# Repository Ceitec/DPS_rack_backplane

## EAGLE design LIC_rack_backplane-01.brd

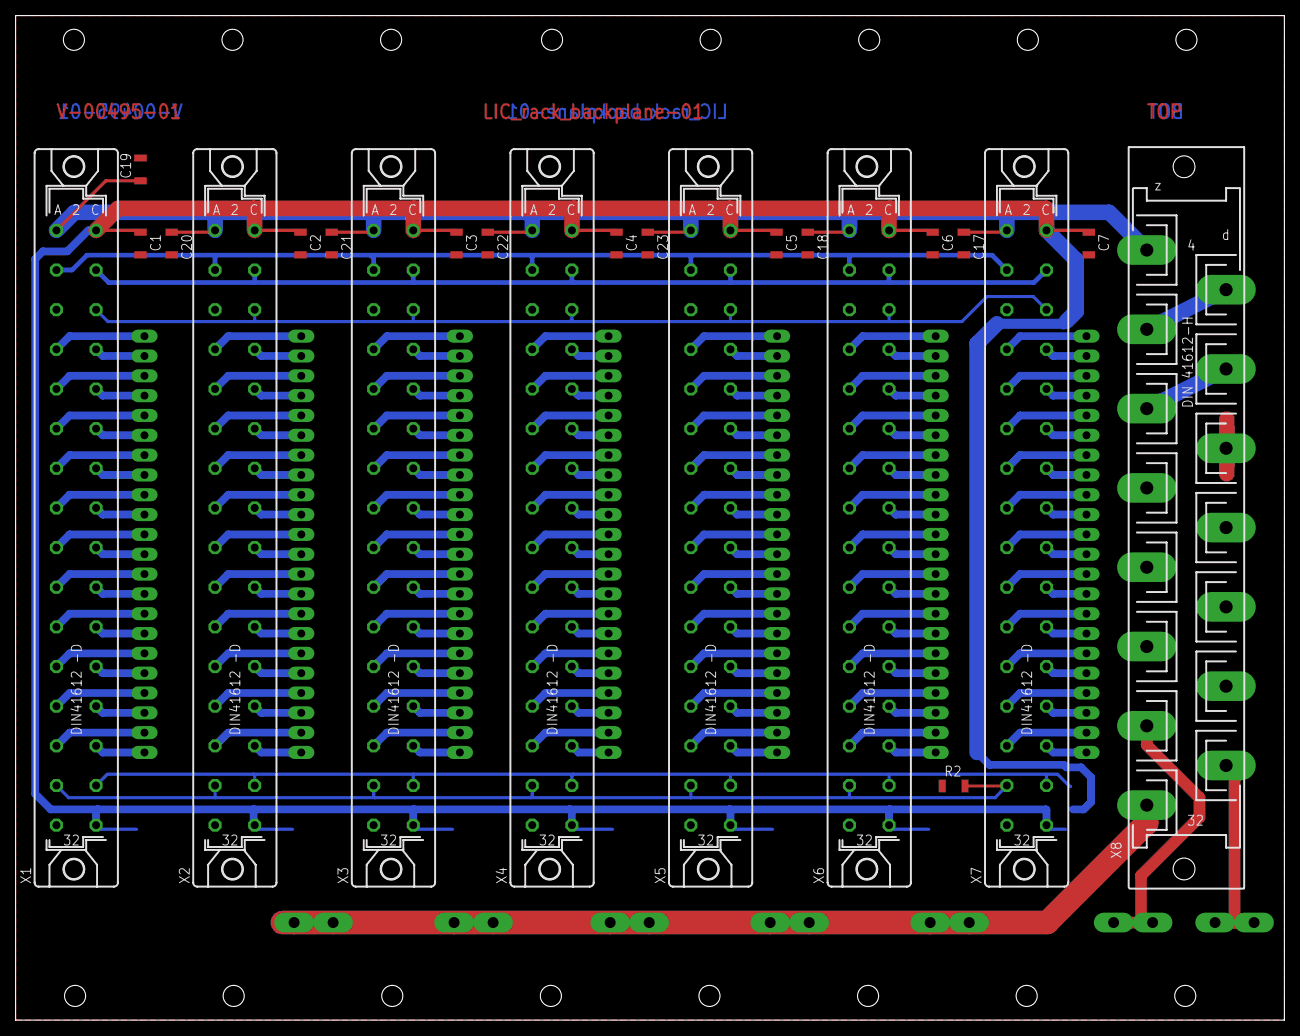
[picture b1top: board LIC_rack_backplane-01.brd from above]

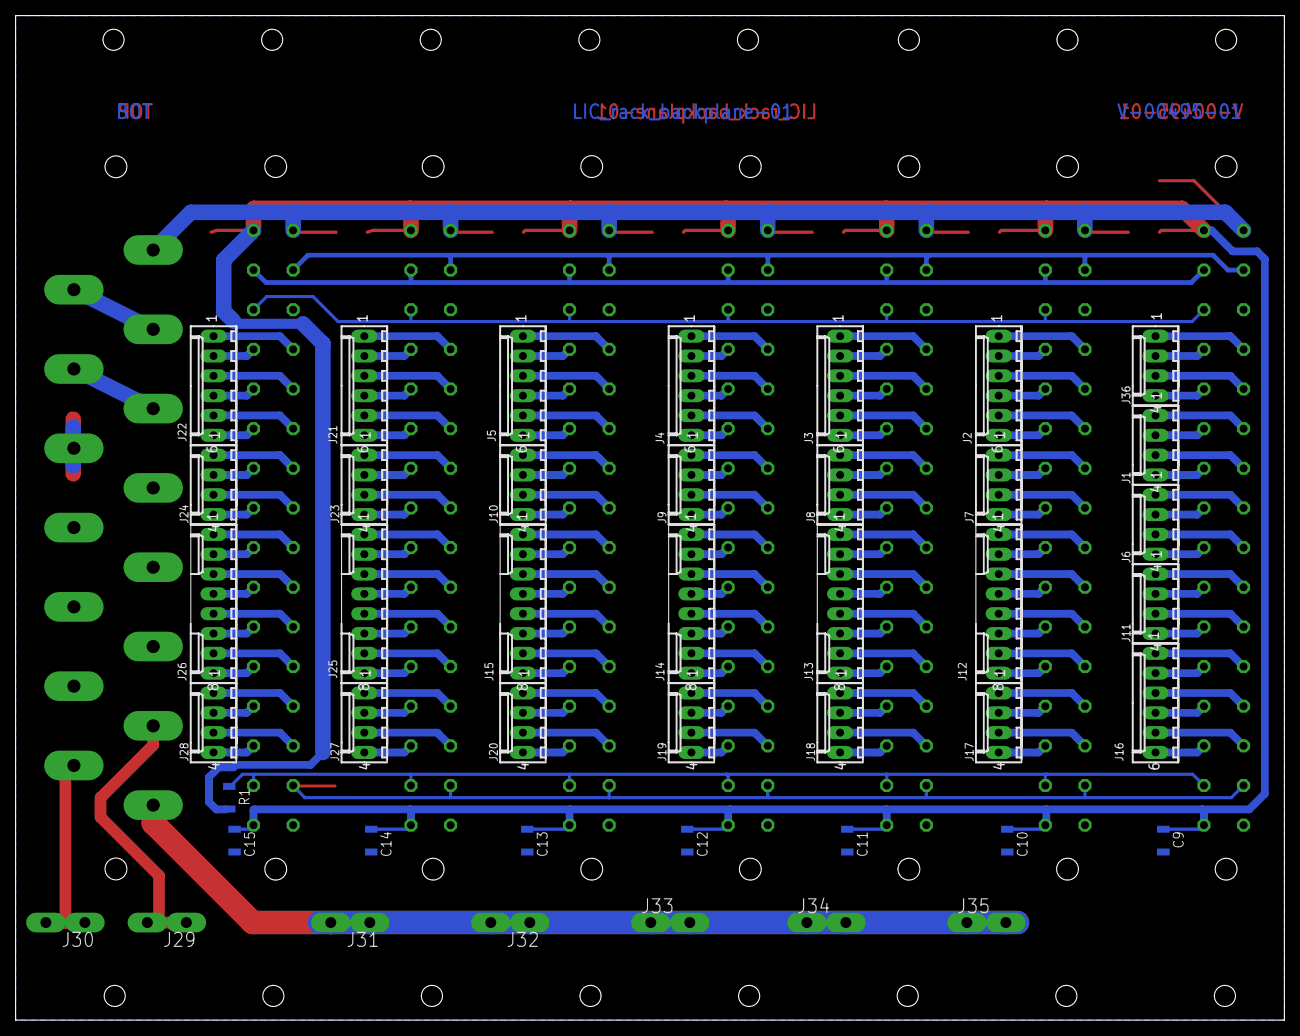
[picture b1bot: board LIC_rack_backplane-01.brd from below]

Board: 2 copper layers, 162.6 x 128.7 mm, 67 parts (44 on the bottom side), 167 nets.

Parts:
C1, C2, C3, C4, C5, C6, C7, C9, C10, C11, C12, C13, C14, C15, C17, C18, C19, C20, C21, C22, C23: 100n; C1206
J1, J6, J7, J8, J9, J10, J11, J17, J18, J19, J20, J23, J24, J27, J28, J36: 22-27-2041-04; 6410-04
J2, J3, J4, J5, J16, J21, J22: 22-27-2061-06; 6410-06
J12, J13, J14, J15, J25, J26: 22-27-2081-08; 6410-08
J29, J30, J31, J32, J33, J34, J35: PIN2F061.100; F061.100
R1, R2: 100k; R1206
X1, X2, X3, X4, X5, X6, X7: FAC32SE; FAC32S
X8: FH15

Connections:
+5V: C1.1, C2.1, C3.1, C4.1, C5.1, C6.1, C7.1, C9.1, C10.1, C11.1, C12.1, C13.1, C14.1, C15.1, R1.2, X1.C2, X1.C32, X2.C2, X2.C32, X3.C2, X3.C32, X4.C2, X4.C32, X5.C2, X5.C32, X6.C2, X6.C32, X7.C2, X7.C32
+12V: X1.A4, X2.A4, X3.A4, X4.A4, X5.A4, X6.A4, X7.A4
+24V: C17.1, C18.1, C19.1, C20.1, C21.1, C22.1, C23.1, X1.A2, X2.A2, X3.A2, X4.A2, X5.A2, X6.A2, X7.A2, X8.4
-12V: X1.C4, X2.C4, X3.C4, X4.C4, X5.C4, X6.C4, X7.C4
GND: C1.2, C2.2, C3.2, C4.2, C5.2, C6.2, C7.2, C9.2, C10.2, C11.2, C12.2, C13.2, C14.2, C15.2, C17.2, C18.2, C19.2, C20.2, C21.2, C22.2, C23.2, R2.1, X1.A6, X1.A32, X2.A6, X2.A32, X3.A6, X3.A32, X4.A6, X4.A32, X5.A6, X5.A32, X6.A6, X6.A32, X7.A6, X7.A32, X8.14
L: J29.A1, J29.A2, X8.28
N: J30.A1, J30.A2, X8.30
unnamed: X8.6, X8.8
unnamed: X8.10, X8.12
unnamed: J16.3, X1.A26
unnamed: J16.4, X1.C26
unnamed: J16.5, X1.A28
unnamed: J2.1, X2.A8
unnamed: J2.2, X2.C8
unnamed: J2.3, X2.A10
unnamed: J2.4, X2.C10
unnamed: J2.5, X2.A12
unnamed: J2.6, X2.C12
unnamed: J7.1, X2.A14
unnamed: J1.1, X1.A12
unnamed: J1.2, X1.C12
unnamed: J1.3, X1.A14
unnamed: J1.4, X1.C14
unnamed: J6.1, X1.A16
unnamed: J13.2, X3.C18
unnamed: J13.3, X3.A20
unnamed: J13.4, X3.C20
unnamed: J13.5, X3.A22
unnamed: J13.6, X3.C22
unnamed: J13.7, X3.A24
unnamed: J13.8, X3.C24
unnamed: J18.1, X3.A26
unnamed: J18.2, X3.C26
unnamed: J18.3, X3.A28
unnamed: J18.4, X3.C28
unnamed: J16.6, X1.C28
unnamed: J36.1, X1.A8
unnamed: J36.2, X1.C8
unnamed: J36.3, X1.A10
unnamed: J36.4, X1.C10
unnamed: J6.2, X1.C16
unnamed: J6.3, X1.A18
unnamed: J6.4, X1.C18
unnamed: J11.1, X1.A20
unnamed: J11.2, X1.C20
unnamed: J11.3, X1.A22
unnamed: J11.4, X1.C22
unnamed: J16.1, X1.A24
unnamed: J16.2, X1.C24
unnamed: J14.2, X4.C18
unnamed: J14.3, X4.A20
unnamed: J14.4, X4.C20
unnamed: J14.5, X4.A22
unnamed: J14.6, X4.C22
unnamed: J14.7, X4.A24
unnamed: J14.8, X4.C24
unnamed: J19.1, X4.A26
unnamed: J19.2, X4.C26
unnamed: J19.3, X4.A28
unnamed: J19.4, X4.C28
unnamed: J15.2, X5.C18
unnamed: J15.3, X5.A20
unnamed: J15.4, X5.C20
unnamed: J15.5, X5.A22
unnamed: J15.6, X5.C22
unnamed: J15.7, X5.A24
unnamed: J15.8, X5.C24
unnamed: J20.1, X5.A26
unnamed: J20.2, X5.C26
unnamed: J20.3, X5.A28
unnamed: J20.4, X5.C28
unnamed: J25.2, X6.C18
unnamed: J25.3, X6.A20
unnamed: J25.4, X6.C20
unnamed: J25.5, X6.A22
unnamed: J25.6, X6.C22
unnamed: J25.7, X6.A24
unnamed: J25.8, X6.C24
unnamed: J27.1, X6.A26
unnamed: J27.2, X6.C26
unnamed: J27.3, X6.A28
unnamed: J27.4, X6.C28
unnamed: J7.2, X2.C14
unnamed: J7.3, X2.A16
unnamed: J7.4, X2.C16
unnamed: J17.1, X2.A26
unnamed: J17.2, X2.C26
unnamed: J17.3, X2.A28
unnamed: J17.4, X2.C28
unnamed: J12.1, X2.A18
unnamed: J12.2, X2.C18
unnamed: J12.3, X2.A20
unnamed: J12.4, X2.C20
unnamed: J12.5, X2.A22
unnamed: J12.6, X2.C22
unnamed: J12.7, X2.A24
unnamed: J12.8, X2.C24
unnamed: J22.1, X7.A8
unnamed: J22.2, X7.C8
unnamed: J22.3, X7.A10
unnamed: J22.4, X7.C10
unnamed: J22.5, X7.A12
unnamed: J22.6, X7.C12
unnamed: J24.1, X7.A14
unnamed: J24.2, X7.C14
unnamed: J24.3, X7.A16
unnamed: J24.4, X7.C16
unnamed: J28.1, X7.A26
unnamed: J28.2, X7.C26
unnamed: J28.3, X7.A28
unnamed: J28.4, X7.C28
unnamed: J26.1, X7.A18
unnamed: J26.2, X7.C18
unnamed: J26.3, X7.A20
unnamed: J26.4, X7.C20
unnamed: J26.5, X7.A22
unnamed: J26.6, X7.C22
unnamed: J26.7, X7.A24
unnamed: J26.8, X7.C24
PE: J31.A1, J31.A2, J32.A1, J32.A2, J33.A1, J33.A2, J34.A1, J34.A2, J35.A1, J35.A2, X8.32
RS+: R1.1, X1.C30, X2.C30, X3.C30, X4.C30, X5.C30, X6.C30, X7.C30
RS-: R2.2, X1.A30, X2.A30, X3.A30, X4.A30, X5.A30, X6.A30, X7.A30
SYNC: X1.C6, X2.C6, X3.C6, X4.C6, X5.C6, X6.C6, X7.C6
U_01_01: J3.1, X3.A8
U_01_02: J3.2, X3.C8
U_01_03: J3.3, X3.A10
U_01_04: J3.4, X3.C10
U_01_05: J3.5, X3.A12
U_01_06: J3.6, X3.C12
U_01_07: J8.1, X3.A14
U_01_08: J8.2, X3.C14
U_01_09: J8.3, X3.A16
U_01_10: J8.4, X3.C16
U_01_11: J13.1, X3.A18
U_01_12: J4.1, X4.A8
U_01_13: J4.2, X4.C8
U_01_14: J4.3, X4.A10
U_01_15: J4.4, X4.C10
U_01_16: J4.5, X4.A12
U_01_17: J4.6, X4.C12
U_01_18: J9.1, X4.A14
U_01_19: J9.2, X4.C14
U_01_20: J9.3, X4.A16
U_01_21: J9.4, X4.C16
U_01_22: J14.1, X4.A18
U_01_23: J5.1, X5.A8
U_01_24: J5.2, X5.C8
U_01_25: J5.3, X5.A10
U_01_26: J5.4, X5.C10
U_01_27: J5.5, X5.A12
U_01_28: J5.6, X5.C12
U_01_29: J10.1, X5.A14
U_01_30: J10.2, X5.C14
U_01_31: J10.3, X5.A16
U_01_32: J10.4, X5.C16
U_01_33: J15.1, X5.A18
U_01_34: J21.1, X6.A8
U_01_35: J21.2, X6.C8
U_01_36: J21.3, X6.A10
U_01_37: J21.4, X6.C10
U_01_38: J21.5, X6.A12
U_01_39: J21.6, X6.C12
U_01_40: J23.1, X6.A14
U_01_41: J23.2, X6.C14
U_01_42: J23.3, X6.A16
U_01_43: J23.4, X6.C16
U_01_44: J25.1, X6.A18

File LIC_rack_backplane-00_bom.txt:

Partlist exported from D:/Michal/Elektronika/projekty/VUT/LIBS_Tescan/DPS_rack_backplane/LIC_rack_backplane-00.sch at 19.6.2014 11:52:37

Qty Value         Device        Parts                                                                                                         GM            code   
16  22-27-2041-04 22-27-2041-04 J6, J7, J8, J9, J10, J16, J17, J18, J19, J20, J24, J25, J26, J30, J31, J32                                                         
8   22-27-2061-06 22-27-2061-06 J1, J2, J3, J4, J5, J21, J22, J23                                                                                                  
8   22-27-2081-08 22-27-2081-08 J11, J12, J13, J14, J15, J27, J28, J29                                                                                             
2   100k          R-EU_R1206    R1, R2                                                                                                        R1206 100K 1% 900-002
24  100n          C-EUC1206     C1, C2, C3, C4, C5, C6, C7, C8, C9, C10, C11, C12, C13, C14, C15, C16, C17, C18, C19, C20, C21, C22, C23, C24 CK 1206 100nF -      
8   FAC32SE       FAC32SE       X1, X2, X3, X4, X5, X6, X7, X8                                                                                                     
1   FH15          FH15          X9                                                                                                                                 
7   PIN2F061.100  PIN2F061.100  J33, J34, J35, J36, J37, J38, J39

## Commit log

2015-08-11 :neckbeard: Added .gitattributes & .gitignore files
2015-08-11 BackPlane
    Zadní propojovací backplane
2015-08-11 Pridani zakazanych koncovek
2015-09-25 Vysoké učení technické v Brně
    Vysoké učení technické v Brně
    Fakulta strojního inženýrství
    Antonínská 548/1
    61669 Brno
    DIČ: CZ00216305
    IČ: 00216305
